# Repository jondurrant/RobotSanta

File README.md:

# RobotSanta

This is a face tracking Santa Head project for my [YouTube channel](https://youtube.com/@drjonea). Built using a Raspberry PI 4 and Raspberry PI Pico.

## Cloning
Please clone with the *--recurse-submodules* switch to include the libraries.

## Pico - Firmware

This is dependent on three libraries:
+ [MicroROS](https://github.com/micro-ROS/micro_ros_raspberrypi_pico_sdk) - Allow Pico to see and communicate with ROS Nodes
+ [FreeRTOS Kernel](https://github.com/FreeRTOS/FreeRTOS-Kernel) - Allow multi threading tasks on Pico
+ [Eigen](https://gitlab.com/libeigen/eigen) - Used to do some Robot maths

To build binary
```
mkdir build
cd build
cmake ..
make
```

### RPI - High-level function

The Raspberry PI needs to be running MicroROS bridget to connect to the Pico.  See the repo [MicroROS](https://github.com/micro-ROS/micro_ros_raspberrypi_pico_sdk) or my [video walkthrough on MicroROS](https://youtu.be/2dGCcT9rxso)

You will also need to install [ROS Humble](https://docs.ros.org/en/humble/Installation.html).

The *py* folder contains two python programms.

## pose.py
This will instruct the head to move to a possition. It takes pitch and yaw as parameters in radians. (-PI/2 to PI/2).

## facePan.py
This uses openCV to detect faces on a camera and instruct the Robot to turn towards that face.

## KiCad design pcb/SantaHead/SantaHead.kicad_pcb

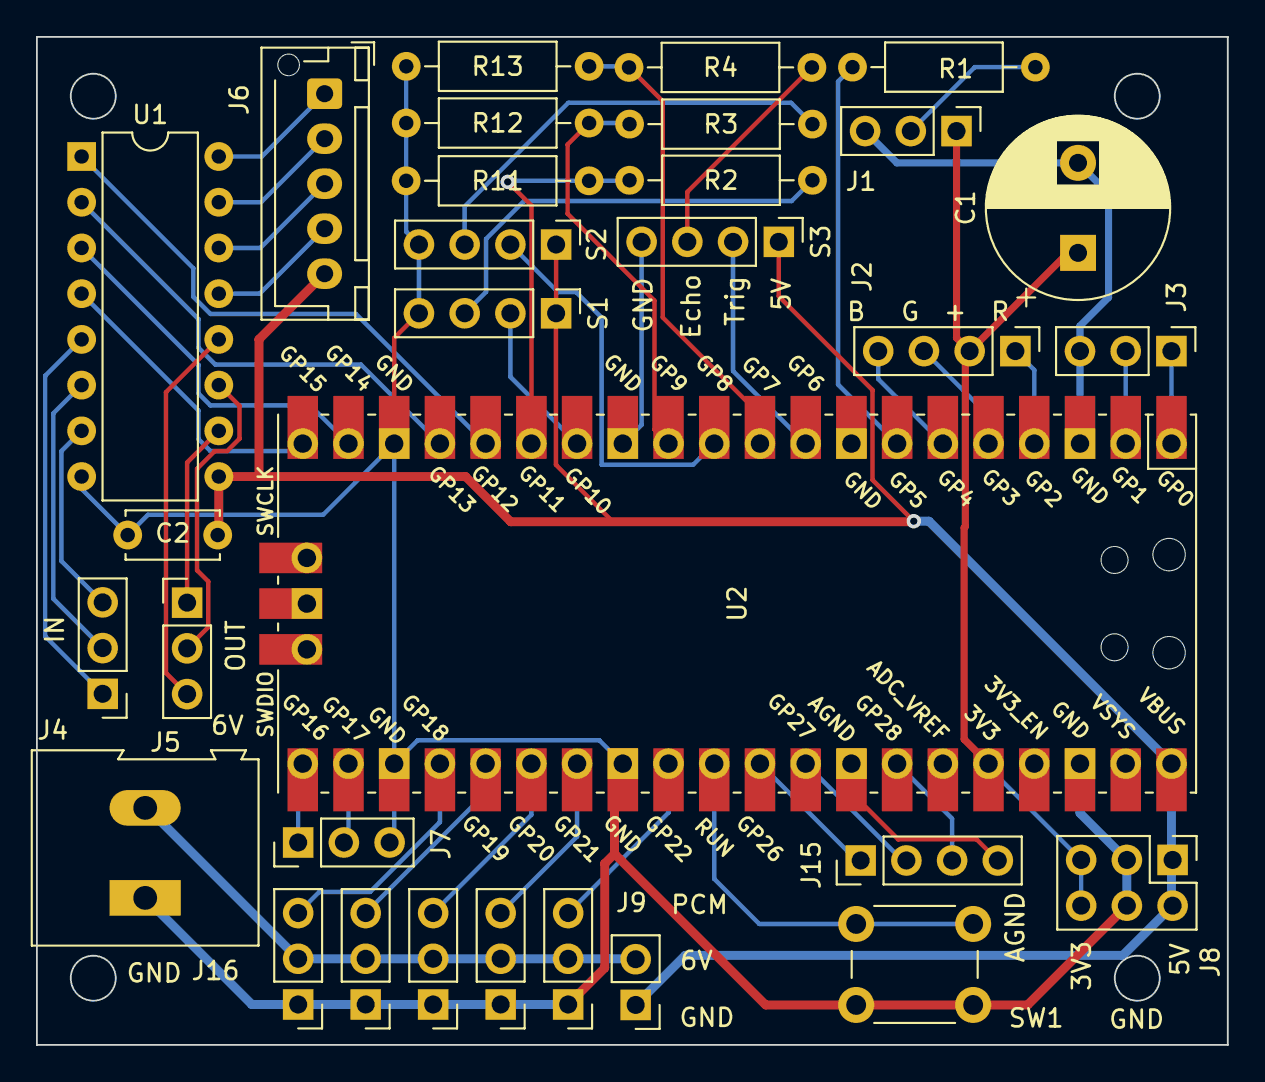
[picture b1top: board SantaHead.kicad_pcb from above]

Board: 2 copper layers, 66.2 x 56.0 mm, 31 parts (0 on the bottom side), 46 nets.

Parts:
C1: C_Polarized; CP_Radial_D10.0mm_P5.00mm
C2: 100nF; C_Disc_D5.0mm_W2.5mm_P5.00mm
J1, J3, J4, J5, J7, J10, J11, J12, J13, J14: Conn_01x03_Male; PinHeader_1x03_P2.54mm_Vertical
J2, J15: Conn_01x04_Male; PinHeader_1x04_P2.54mm_Vertical
J6: Conn_01x05; JST_XH_B5B-XH-AM_1x05_P2.50mm_Vertical
J8: Conn_02x03_Odd_Even; PinHeader_2x03_P2.54mm_Vertical
J9: Conn_01x02_Male; PinHeader_1x02_P2.54mm_Vertical
J16: Screw_Terminal_01x02; TerminalBlock_Altech_AK300-2_P5.00mm
R1: 220R; R_Axial_DIN0207_L6.3mm_D2.5mm_P10.16mm_Horizontal
R2, R3, R4: 2K2; R_Axial_DIN0207_L6.3mm_D2.5mm_P10.16mm_Horizontal
R11, R12, R13: 3k3; R_Axial_DIN0207_L6.3mm_D2.5mm_P10.16mm_Horizontal
S1, S2, S3: HCSR04; PinHeader_1x04_P2.54mm_Vertical
SW1: SW_Push; SW_PUSH_6mm
U1: ULN2003; DIP-16_W7.62mm
U2: Pico; RPi_Pico_SMD_TH

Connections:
+3.3V: C1.1, J1.1, J2.2, J8.5, J8.6, U2.36 (3V3)
+5V: C2.1, J6.5, J8.1, J8.2, J9.1, S1.1 (VCC), S2.1 (VCC), S3.1 (VCC), U1.9 (COM), U2.40 (VBUS)
+6V: J9.2, J10.2, J11.2, J12.2, J13.2, J14.2, J16.2
GND: C1.2, C2.2, J1.3, J3.3, J7.3, J8.3, J8.4, J10.1, J11.1, J12.1, J13.1, J14.1, J16.1, R11.2, R12.2, R13.2, S1.4 (GND), S2.4 (GND), S3.4 (GND), SW1.2, U1.8 (GND), U2.3 (GND), U2.13 (GND), U2.18 (GND), U2.23 (GND), U2.28 (GND), U2.38 (GND)
unnamed: J1.2, R1.1
unnamed: J2.1, U2.4 (GPIO2)
unnamed: J2.3, U2.5 (GPIO3)
unnamed: J2.4, U2.6 (GPIO4)
unnamed: J3.1, U2.1 (GPIO0)
unnamed: J3.2, U2.2 (GPIO1)
unnamed: J6.1, U1.16 (O1)
unnamed: J6.2, U1.15 (O2)
unnamed: J6.3, U1.14 (O3)
unnamed: J6.4, U1.13 (O4)
unnamed: J10.3, U2.29 (GPIO22)
unnamed: J11.3, U2.27 (GPIO21)
unnamed: J12.3, U2.26 (GPIO20)
unnamed: J13.3, U2.25 (GPIO19)
unnamed: J14.3, U2.24 (GPIO18)
unnamed: J15.1 (VCC), U2.31 (GPIO26_ADC0)
unnamed: J15.3 (ECHO), U2.34 (GPIO28_ADC2)
unnamed: R1.2, U2.7 (GPIO5)
unnamed: R2.1, S1.3 (ECHO)
unnamed: R3.1, S2.3 (ECHO)
unnamed: R4.1, S3.3 (ECHO)
unnamed: R2.2, R11.1, U2.15 (GPIO11)
unnamed: R3.2, R12.1, U2.12 (GPIO9)
unnamed: R4.2, R13.1, U2.10 (GPIO7)
unnamed: S1.2 (TRIG), U2.14 (GPIO10)
unnamed: S2.2 (TRIG), U2.11 (GPIO8)
unnamed: S3.2 (TRIG), U2.9 (GPIO6)
unnamed: SW1.1, U2.30 (RUN)
unnamed: J4.1, U1.5 (I5)
unnamed: J4.2, U1.6 (I6)
unnamed: J4.3, U1.7 (I7)
unnamed: J5.1, U1.10 (O7)
unnamed: J5.2, U1.11 (O6)
unnamed: J5.3, U1.12 (O5)
unnamed: U1.1 (I1), U2.16 (GPIO12)
unnamed: U1.2 (I2), U2.17 (GPIO13)
unnamed: U1.3 (I3), U2.19 (GPIO14)
unnamed: U1.4 (I4), U2.20 (GPIO15)
unnamed: J7.1, U2.21 (GPIO16)
unnamed: J7.2, U2.22 (GPIO17)
unnamed: J15.2 (TRIG), U2.32 (GPIO27_ADC1)
unnamed: J15.4 (GND), U2.33 (AGND)

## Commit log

2023-11-28 Video Version
2023-11-30 Face recognition example added
2023-11-30 Bump requests from 2.25.1 to 2.31.0 in /py
    Bumps [requests](https://github.com/psf/requests) from 2.25.1 to 2.31.0.
    - [Release notes](https://github.com/psf/requests/releases)
    - [Changelog](https://github.com/psf/requests/blob/main/HISTORY.md)
    - [Commits](https://github.com/psf/requests/compare/v2.25.1...v2.31.0)
    ---
    updated-dependencies:
2023-11-30 Bump numpy from 1.21.5 to 1.22.0 in /py
    Bumps [numpy](https://github.com/numpy/numpy) from 1.21.5 to 1.22.0.
    - [Release notes](https://github.com/numpy/numpy/releases)
    - [Changelog](https://github.com/numpy/numpy/blob/main/doc/RELEASE_WALKTHROUGH.rst)
    - [Commits](https://github.com/numpy/numpy/compare/v1.21.5...v1.22.0)
    ---
    updated-dependencies:
2023-11-30 Bump twisted from 22.1.0 to 23.10.0 in /py
    Bumps [twisted](https://github.com/twisted/twisted) from 22.1.0 to 23.10.0.
    - [Release notes](https://github.com/twisted/twisted/releases)
    - [Changelog](https://github.com/twisted/twisted/blob/trunk/NEWS.rst)
    - [Commits](https://github.com/twisted/twisted/compare/twisted-22.1.0...twisted-23.10.0)
    ---
    updated-dependencies:
